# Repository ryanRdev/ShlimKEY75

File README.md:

# ShlimKEY75
A 75% Keyboard with a Rotary Encoder :3

| PCB | Schematic | 3D Model |
|-----------|-----------|-----------|
 |  | 

# Why did I make this?
- 60% Keyboards suck
- I need a volume knob
- It looks cool :3

# Bill of Materials

| Price     | Name                                 | Quantity |
|-----------|--------------------------------------|----------|
| $2.73     | Raspberry Pi Pico                    | 1                   |
| $24.99    | Gateron Milky Yellow Switches        |  90 (81 needed)     |
| $10.00    | DUROCK Stabilizers                   | 5
| $30.99    | Transparent Keycaps                  | 100 (81 needed)
| $1.04     | Diodes                               | 100 (81 needed)     |
| $2.63     | Alps EC11E Rotary Encoder            | 5 (1 needed)        |
| $0.99     | M3 16mm Fastening Screws      | 40 (4 needed) |
| ~$5.00    | 3D Print from Printing Legion |
| **$78.37** | **Total**
| |
|     | JLCPCB Checkout                      |                     |
| $20.70    | PCB Total
| $25.23    | Shipping Estimate
| **$44.75**| **Total**
|  |
| **$123.12**| **Grand Total**

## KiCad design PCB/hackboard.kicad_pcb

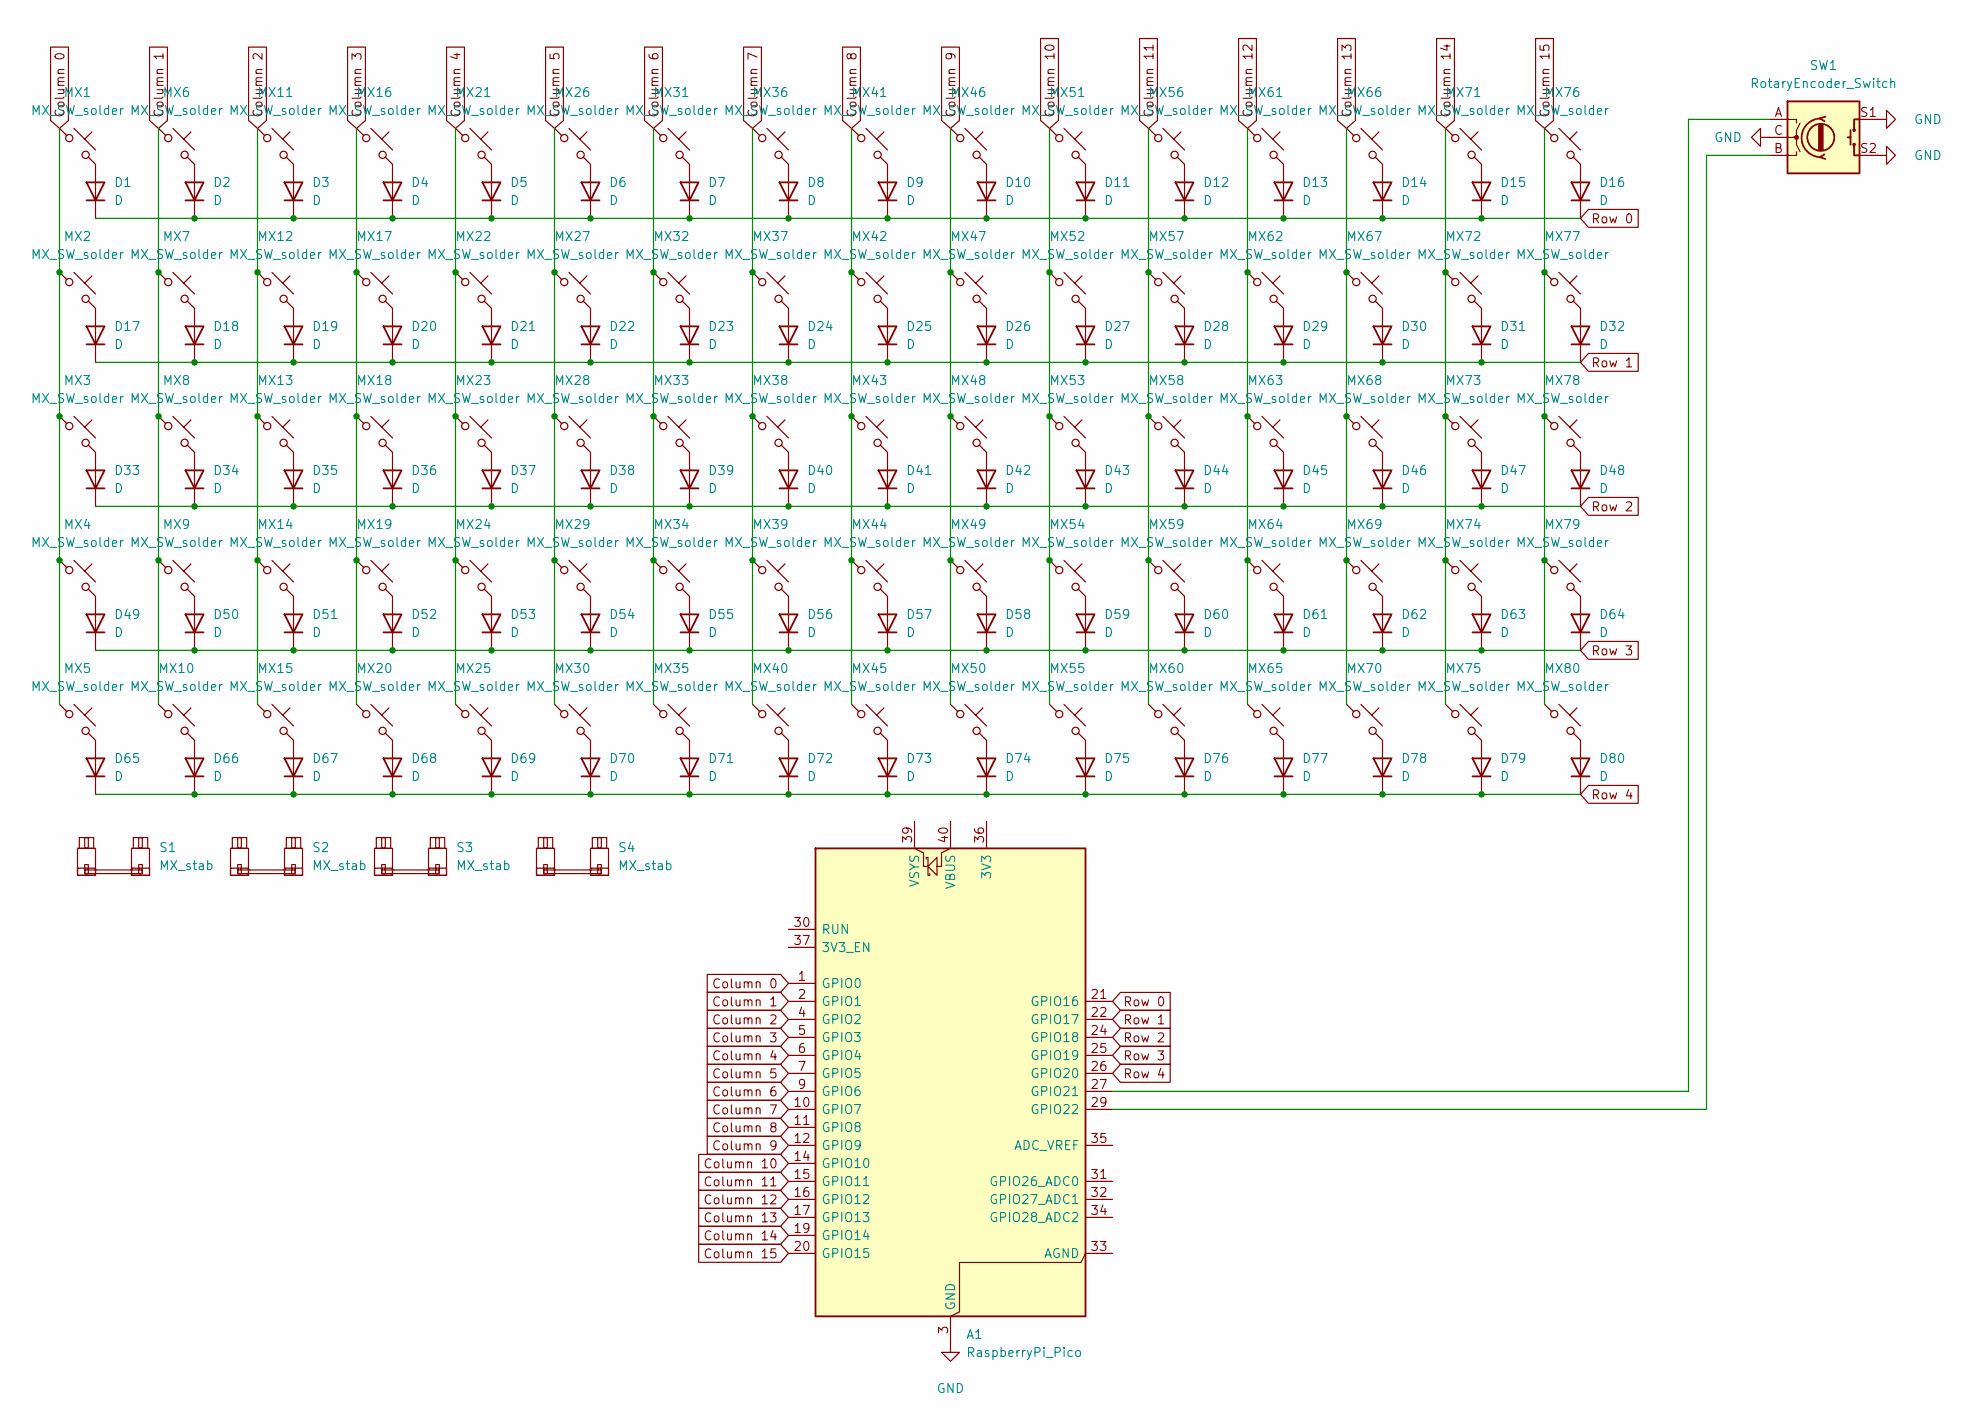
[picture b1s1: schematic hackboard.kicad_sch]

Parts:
A1: RaspberryPi_Pico; RaspberryPi_Pico_Common_Unspecified
D1, D2, D3, D4, D5, D6, D7, D8, D9, D10, D11, D12, D13, D14, D15, D16, D17, D18, D19, D20, D21, D22, D23, D24, D25, D26, D27, D28, D29, D30, D31, D32, D33, D34, D35, D36, D37, D38, D39, D40, D41, D42, D43, D44, D45, D46, D47, D48, D49, D50, D51, D52, D53, D54, D55, D56, D57, D58, D59, D60, D61, D62, D63, D64, D65, D66, D67, D68, D69, D70, D71, D72, D73, D74, D75, D76, D77, D78, D79, D80: D; D_SOD-123
MX1, MX2, MX3, MX4, MX5, MX6, MX7, MX8, MX9, MX10, MX11, MX12, MX13, MX14, MX15, MX16, MX17, MX18, MX19, MX20, MX21, MX22, MX23, MX24, MX25, MX26, MX27, MX28, MX29, MX30, MX31, MX32, MX33, MX34, MX35, MX36, MX37, MX38, MX39, MX40, MX41, MX42, MX43, MX44, MX45, MX46, MX47, MX48, MX49, MX50, MX51, MX52, MX53, MX54, MX55, MX56, MX57, MX58, MX59, MX60, MX61, MX62, MX63, MX64, MX65, MX66, MX67, MX68, MX69, MX70, MX71, MX72, MX73, MX74, MX75, MX76, MX77, MX78, MX79, MX80: MX_SW_solder; SW_MX_1u
S1: MX_stab; STAB_MX_P_6.25u
S2, S3: MX_stab; STAB_MX_P_2.25u
S4: MX_stab; STAB_MX_P_2u
SW1: RotaryEncoder_Switch; RotaryEncoder_Alps_EC11E-Switch_Vertical_H20mm

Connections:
Column 0: A1.1 (GPIO0), MX1.1, MX2.1, MX3.1, MX4.1, MX5.1
Column 1: A1.2 (GPIO1), MX6.1, MX7.1, MX8.1, MX9.1, MX10.1
Column 2: A1.4 (GPIO2), MX11.1, MX12.1, MX13.1, MX14.1, MX15.1
Column 3: A1.5 (GPIO3), MX16.1, MX17.1, MX18.1, MX19.1, MX20.1
Column 4: A1.6 (GPIO4), MX21.1, MX22.1, MX23.1, MX24.1, MX25.1
Column 5: A1.7 (GPIO5), MX26.1, MX27.1, MX28.1, MX29.1, MX30.1
Column 6: A1.9 (GPIO6), MX31.1, MX32.1, MX33.1, MX34.1, MX35.1
Column 7: A1.10 (GPIO7), MX36.1, MX37.1, MX38.1, MX39.1, MX40.1
Column 8: A1.11 (GPIO8), MX41.1, MX42.1, MX43.1, MX44.1, MX45.1
Column 9: A1.12 (GPIO9), MX46.1, MX47.1, MX48.1, MX49.1, MX50.1
Column 10: A1.14 (GPIO10), MX51.1, MX52.1, MX53.1, MX54.1, MX55.1
Column 11: A1.15 (GPIO11), MX56.1, MX57.1, MX58.1, MX59.1, MX60.1
Column 12: A1.16 (GPIO12), MX61.1, MX62.1, MX63.1, MX64.1, MX65.1
Column 13: A1.17 (GPIO13), MX66.1, MX67.1, MX68.1, MX69.1, MX70.1
Column 14: A1.19 (GPIO14), MX71.1, MX72.1, MX73.1, MX74.1, MX75.1
Column 15: A1.20 (GPIO15), MX76.1, MX77.1, MX78.1, MX79.1, MX80.1
GND: A1.3 (GND), A1.8 (GND), A1.13 (GND), A1.18 (GND), A1.23 (GND), A1.28 (GND), A1.38 (GND), SW1.C, SW1.S1, SW1.S2
unnamed: A1.27 (GPIO21), SW1.A
unnamed: A1.29 (GPIO22), SW1.B
unnamed: D1.2 (A), MX1.2
unnamed: D2.2 (A), MX6.2
unnamed: D3.2 (A), MX11.2
unnamed: D4.2 (A), MX16.2
unnamed: D5.2 (A), MX21.2
unnamed: D6.2 (A), MX26.2
unnamed: D7.2 (A), MX31.2
unnamed: D8.2 (A), MX36.2
unnamed: D9.2 (A), MX41.2
unnamed: D10.2 (A), MX46.2
unnamed: D11.2 (A), MX51.2
unnamed: D12.2 (A), MX56.2
unnamed: D13.2 (A), MX61.2
unnamed: D14.2 (A), MX66.2
unnamed: D15.2 (A), MX71.2
unnamed: D16.2 (A), MX76.2
unnamed: D17.2 (A), MX2.2
unnamed: D18.2 (A), MX7.2
unnamed: D19.2 (A), MX12.2
unnamed: D20.2 (A), MX17.2
unnamed: D21.2 (A), MX22.2
unnamed: D22.2 (A), MX27.2
unnamed: D23.2 (A), MX32.2
unnamed: D24.2 (A), MX37.2
unnamed: D25.2 (A), MX42.2
unnamed: D26.2 (A), MX47.2
unnamed: D27.2 (A), MX52.2
unnamed: D28.2 (A), MX57.2
unnamed: D29.2 (A), MX62.2
unnamed: D30.2 (A), MX67.2
unnamed: D31.2 (A), MX72.2
unnamed: D32.2 (A), MX77.2
unnamed: D33.2 (A), MX3.2
unnamed: D34.2 (A), MX8.2
unnamed: D35.2 (A), MX13.2
unnamed: D36.2 (A), MX18.2
unnamed: D37.2 (A), MX23.2
unnamed: D38.2 (A), MX28.2
unnamed: D39.2 (A), MX33.2
unnamed: D40.2 (A), MX38.2
unnamed: D41.2 (A), MX43.2
unnamed: D42.2 (A), MX48.2
unnamed: D43.2 (A), MX53.2
unnamed: D44.2 (A), MX58.2
unnamed: D45.2 (A), MX63.2
unnamed: D46.2 (A), MX68.2
unnamed: D47.2 (A), MX73.2
unnamed: D48.2 (A), MX78.2
unnamed: D49.2 (A), MX4.2
unnamed: D50.2 (A), MX9.2
unnamed: D51.2 (A), MX14.2
unnamed: D52.2 (A), MX19.2
unnamed: D53.2 (A), MX24.2
unnamed: D54.2 (A), MX29.2
unnamed: D55.2 (A), MX34.2
unnamed: D56.2 (A), MX39.2
unnamed: D57.2 (A), MX44.2
unnamed: D58.2 (A), MX49.2
unnamed: D59.2 (A), MX54.2
unnamed: D60.2 (A), MX59.2
unnamed: D61.2 (A), MX64.2
unnamed: D62.2 (A), MX69.2
unnamed: D63.2 (A), MX74.2
unnamed: D64.2 (A), MX79.2
unnamed: D65.2 (A), MX5.2
unnamed: D66.2 (A), MX10.2
unnamed: D67.2 (A), MX15.2
unnamed: D68.2 (A), MX20.2
unnamed: D69.2 (A), MX25.2
unnamed: D70.2 (A), MX30.2
unnamed: D71.2 (A), MX35.2
unnamed: D72.2 (A), MX40.2
unnamed: D73.2 (A), MX45.2
unnamed: D74.2 (A), MX50.2
unnamed: D75.2 (A), MX55.2
unnamed: D76.2 (A), MX60.2
unnamed: D77.2 (A), MX65.2
unnamed: D78.2 (A), MX70.2
unnamed: D79.2 (A), MX75.2
unnamed: D80.2 (A), MX80.2
Row 0: A1.21 (GPIO16), D1.1 (K), D2.1 (K), D3.1 (K), D4.1 (K), D5.1 (K), D6.1 (K), D7.1 (K), D8.1 (K), D9.1 (K), D10.1 (K), D11.1 (K), D12.1 (K), D13.1 (K), D14.1 (K), D15.1 (K), D16.1 (K)
Row 1: A1.22 (GPIO17), D17.1 (K), D18.1 (K), D19.1 (K), D20.1 (K), D21.1 (K), D22.1 (K), D23.1 (K), D24.1 (K), D25.1 (K), D26.1 (K), D27.1 (K), D28.1 (K), D29.1 (K), D30.1 (K), D31.1 (K), D32.1 (K)
Row 2: A1.24 (GPIO18), D33.1 (K), D34.1 (K), D35.1 (K), D36.1 (K), D37.1 (K), D38.1 (K), D39.1 (K), D40.1 (K), D41.1 (K), D42.1 (K), D43.1 (K), D44.1 (K), D45.1 (K), D46.1 (K), D47.1 (K), D48.1 (K)
Row 3: A1.25 (GPIO19), D49.1 (K), D50.1 (K), D51.1 (K), D52.1 (K), D53.1 (K), D54.1 (K), D55.1 (K), D56.1 (K), D57.1 (K), D58.1 (K), D59.1 (K), D60.1 (K), D61.1 (K), D62.1 (K), D63.1 (K), D64.1 (K)
Row 4: A1.26 (GPIO20), D65.1 (K), D66.1 (K), D67.1 (K), D68.1 (K), D69.1 (K), D70.1 (K), D71.1 (K), D72.1 (K), D73.1 (K), D74.1 (K), D75.1 (K), D76.1 (K), D77.1 (K), D78.1 (K), D79.1 (K), D80.1 (K)

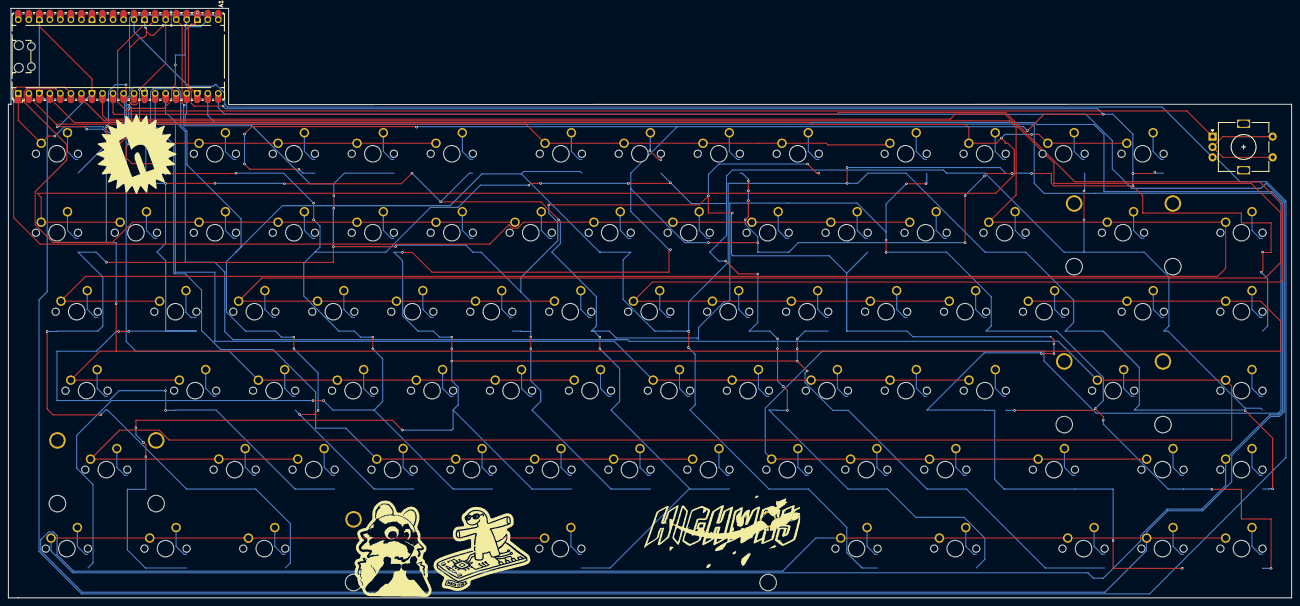
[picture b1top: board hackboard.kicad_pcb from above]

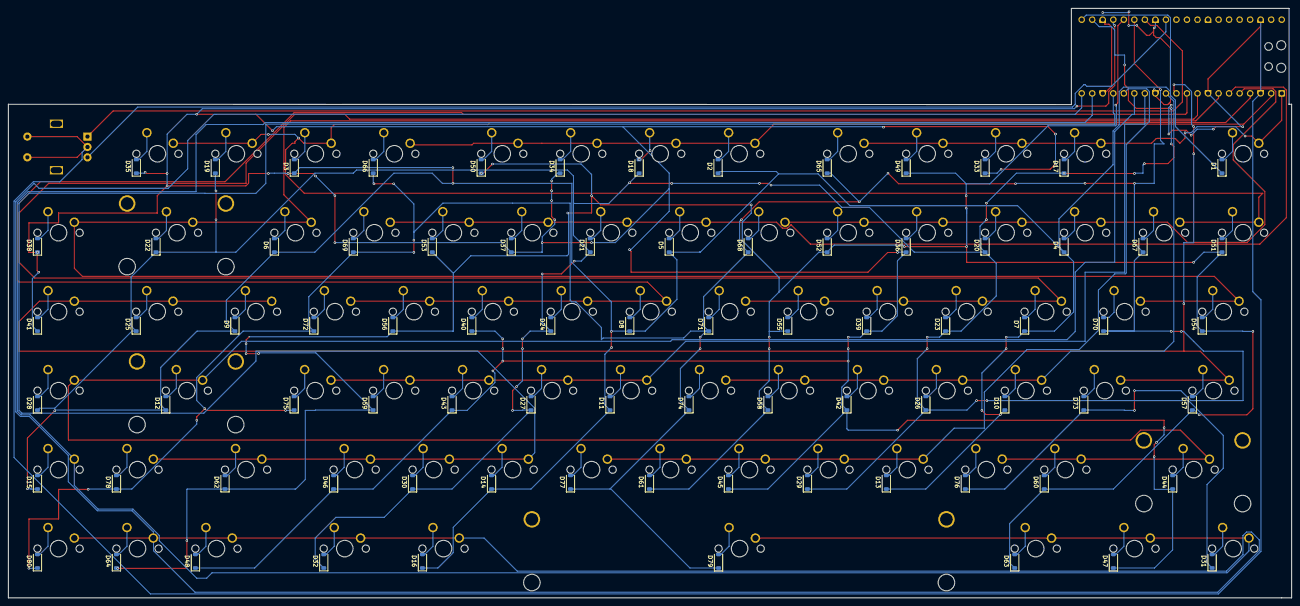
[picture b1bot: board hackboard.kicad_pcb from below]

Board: 2 copper layers, 309.6 x 142.2 mm, 166 parts (80 on the bottom side), 104 nets.

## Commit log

2025-07-22 Edit Journal, Edit README, Upload Files
